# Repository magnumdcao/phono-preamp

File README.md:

# phono-preamp
The PCB design is largely based on the one present in "Build an External Phonograph Preamplifier" by Bill Christie.

PCB design suite: KiCad v5.1.12
Board layer: 2
Amplifier chip: OPA1604, originally LME49740

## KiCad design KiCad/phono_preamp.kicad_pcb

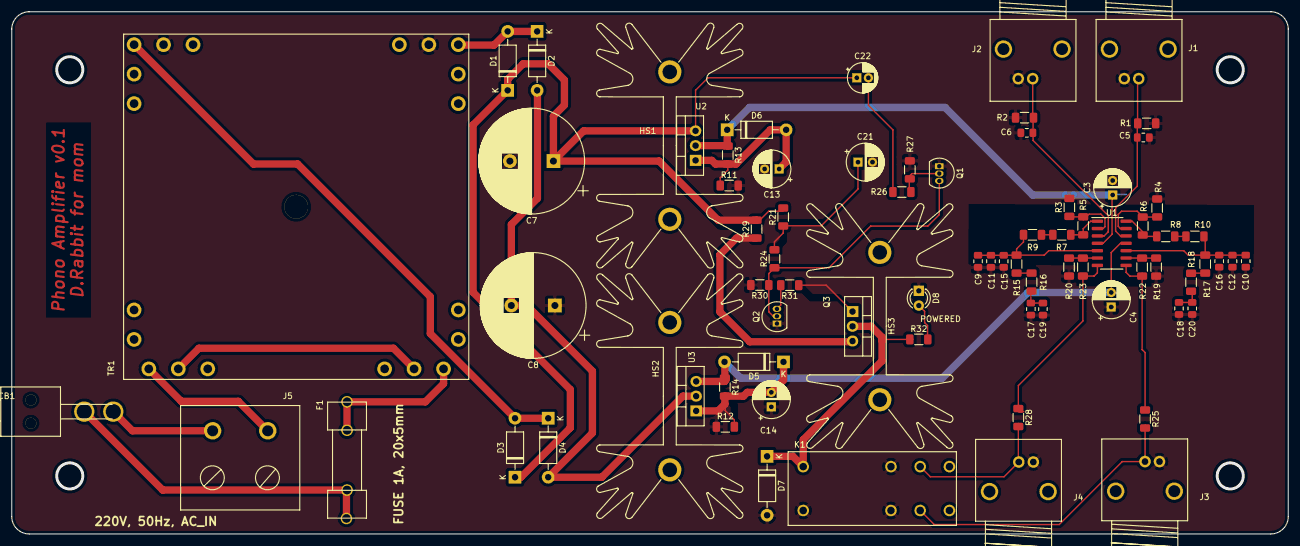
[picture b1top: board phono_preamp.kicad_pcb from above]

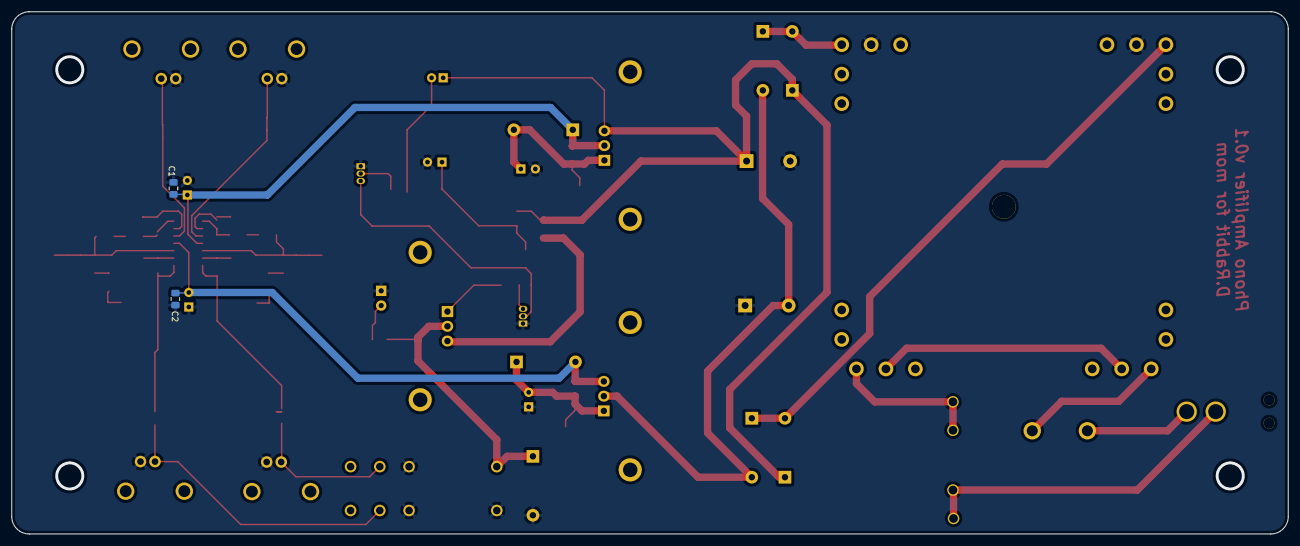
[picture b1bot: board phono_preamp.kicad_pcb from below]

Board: 2 copper layers, 220.0 x 90.0 mm, 80 parts (2 on the bottom side), 43 nets.

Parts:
C1, C2: 100nF; C_0805_2012Metric_Pad1.18x1.45mm_HandSolder
C3, C4: 68uF,35V; CP_Radial_D6.3mm_P2.50mm
C5, C6: 200pF; C_0805_2012Metric_Pad1.18x1.45mm_HandSolder
C7, C8: 3300uF,35V; CP_Radial_D18.0mm_P7.50mm
C9, C10: 500pF; C_0805_2012Metric_Pad1.18x1.45mm_HandSolder
C11, C12, C19, C20: 47nF; C_0805_2012Metric_Pad1.18x1.45mm_HandSolder
C13, C14, C21: 47uF, 50V; CP_Radial_D6.3mm_P2.50mm
C15, C16: 22nF; C_0805_2012Metric_Pad1.18x1.45mm_HandSolder
C17, C18: 33nF; C_0805_2012Metric_Pad1.18x1.45mm_HandSolder
C22: 15uF; CP_Radial_D5.0mm_P2.00mm
CB1: CircuitBreaker_1P; STB_Button_Switch
D1, D2, D3, D4, D5, D6, D7: 1N4007; D_DO-41_SOD81_P10.16mm_Horizontal
D8: LED; LED_D3.0mm_FlatTop
F1: Fuse; FUSE_HOLDER_520
HS1, HS2, HS3: Heatsink; Heatsink_Fischer_SK129-STS_42x25mm_2xDrill2.5mm
J1: RCA_RIN; RCA_Aucharm
J2: RCA_LIN; RCA_Aucharm
J3: RCA_ROUT; RCA_Aucharm
J4: RCA_LOUT; RCA_Aucharm
J5: Conn_01x02_Female; HB-9500
K1: RELAY_DPDT; JQX-115F-2ZS4
Q1, Q2: Q_NPN_EBC; TO-92L_Inline
Q3: TIP42C; TO-220-3_Vertical
R1, R2, R30: 47k; R_1206_3216Metric_Pad1.30x1.75mm_HandSolder
R3, R4, R19, R20: 330; R_1206_3216Metric_Pad1.30x1.75mm_HandSolder
R5, R6, R22, R23: 3.3k; R_1206_3216Metric_Pad1.30x1.75mm_HandSolder
R7, R8: 26.1k; R_1206_3216Metric_Pad1.30x1.75mm_HandSolder
R9, R10: 909; R_1206_3216Metric_Pad1.30x1.75mm_HandSolder
R11, R12, R24, R31: 4.7k; R_1206_3216Metric_Pad1.30x1.75mm_HandSolder
R13, R14, R29: 470; R_1206_3216Metric_Pad1.30x1.75mm_HandSolder
R15, R17: 3.83k; R_1206_3216Metric_Pad1.30x1.75mm_HandSolder
R16, R18, R25, R28: 100; R_1206_3216Metric_Pad1.30x1.75mm_HandSolder
R21: 200k; R_1206_3216Metric_Pad1.30x1.75mm_HandSolder
R26: 10k; R_1206_3216Metric_Pad1.30x1.75mm_HandSolder
R27: 10; R_1206_3216Metric_Pad1.30x1.75mm_HandSolder
R32: 1k; R_1206_3216Metric_Pad1.30x1.75mm_HandSolder
TR1: YHDC_2P2S
U1: OPA1604; SOIC-14_3.9x8.7mm_P1.27mm
U2: LM317_TO-220; TO-220-3_Vertical
U3: LM337_TO220; TO-220-3_Vertical

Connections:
GND: C1.2, C2.1, C3.2, C4.1, C5.2, C6.2, C7.2, C8.1, C9.1, C10.1, C11.1, C12.1, C13.2, C14.1, C15.1, C16.1, C17.2, C18.2, C19.2, C20.2, C21.2, D7.2, D8.1, J1.2, J2.2, J3.2, J4.2, K1.2, K1.3, K1.6, Q1.1, Q2.1, R1.2, R2.2, R3.2, R4.2, R11.2, R12.1, R19.1, R20.2, R27.2, R30.2, TR1.12, TR1.13
unnamed: C5.1, J1.1, R1.1, U1.12
unnamed: C6.1, J2.1, R2.1, U1.3
unnamed: C8.2, D2.2, D4.2, U3.2
unnamed: C10.2, C12.2, C16.2, R10.2, R17.1, U1.10
unnamed: C9.2, C11.2, C15.2, R9.2, R15.1, U1.5
unnamed: C13.1, D6.2, R11.1, R13.2, U2.1
unnamed: C14.2, D5.1, R12.2, R14.2, U3.1
unnamed: C17.1, C19.1, R16.2
unnamed: C18.1, C20.1, R18.2
unnamed: C21.1, R21.1, R24.2
unnamed: C22.2, R26.1
unnamed: CB1.1, F1.2
unnamed: CB1.2, J5.2
unnamed: D1.2, D2.1, TR1.11
unnamed: D3.2, D4.1, TR1.14
unnamed: D7.1, K1.1, Q3.2, R32.1
unnamed: D8.2, R32.2
unnamed: F1.1, TR1.6
unnamed: J3.1, K1.7, R25.2
unnamed: J4.1, K1.4, R28.2
unnamed: J5.1, TR1.3
unnamed: Q1.2, R26.2, R27.1
unnamed: Q1.3, Q2.2, R24.1, R30.1
unnamed: Q2.3, R31.2
unnamed: Q3.1, R31.1
unnamed: Q3.3, R29.1
unnamed: R3.1, R5.1, U1.2
unnamed: R4.1, R6.2, U1.13
unnamed: R5.2, R7.1, U1.1
unnamed: R6.1, R8.1, U1.14
unnamed: R7.2, R9.1
unnamed: R8.2, R10.1
unnamed: R15.2, R16.1
unnamed: R17.2, R18.1
unnamed: R19.2, R22.1, U1.9
unnamed: R20.1, R23.1, U1.6
unnamed: R22.2, R25.1, U1.8
unnamed: R23.2, R28.1, U1.7
unnamed: TR1.4, TR1.5
V+: C1.1, C3.1, D6.1, R13.1, U1.4, U2.2
V+_RAW: C7.1, C22.1, D1.1, D3.1, R21.2, R29.2, U2.3
V-: C2.2, C4.2, D5.2, R14.1, U1.11, U3.3

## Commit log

2021-12-01 Added initial schematic and board design.
